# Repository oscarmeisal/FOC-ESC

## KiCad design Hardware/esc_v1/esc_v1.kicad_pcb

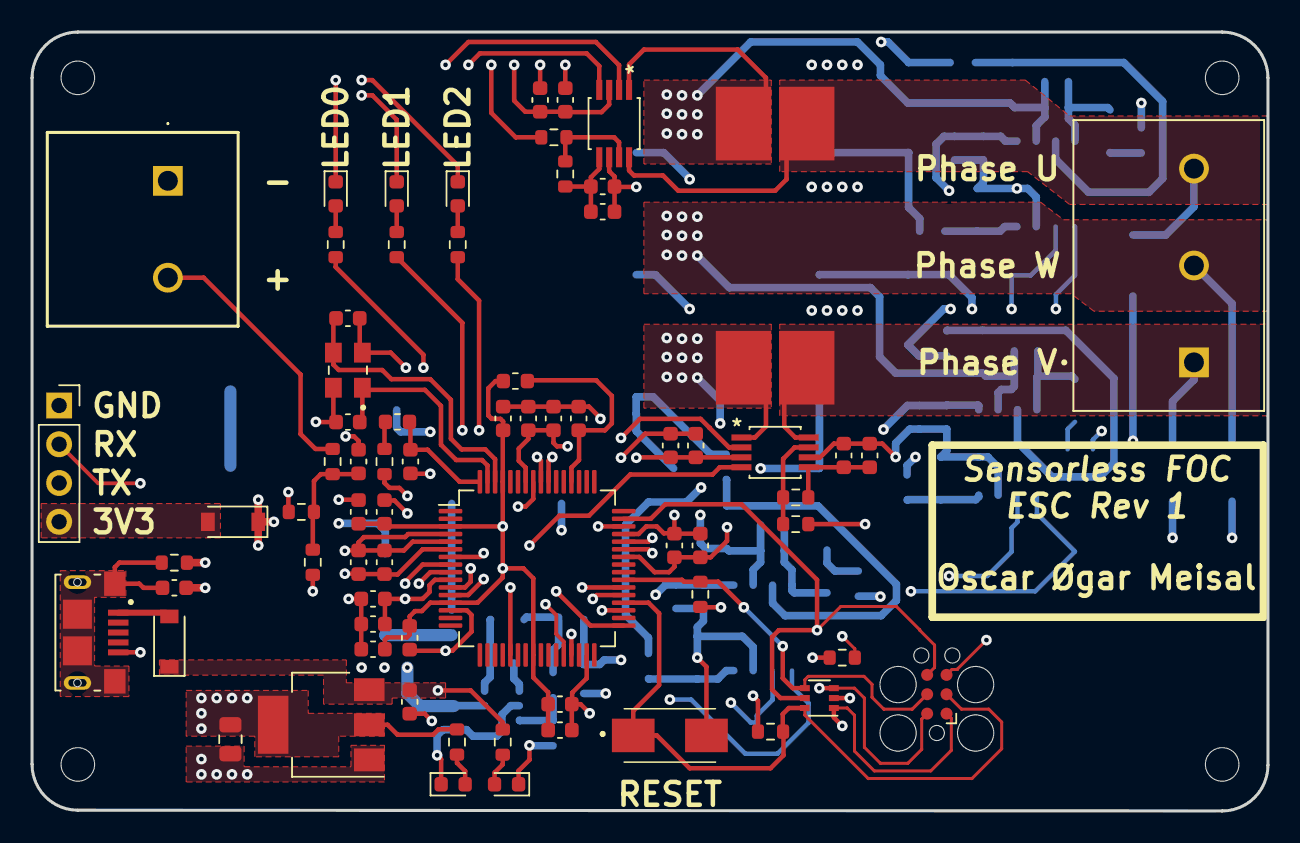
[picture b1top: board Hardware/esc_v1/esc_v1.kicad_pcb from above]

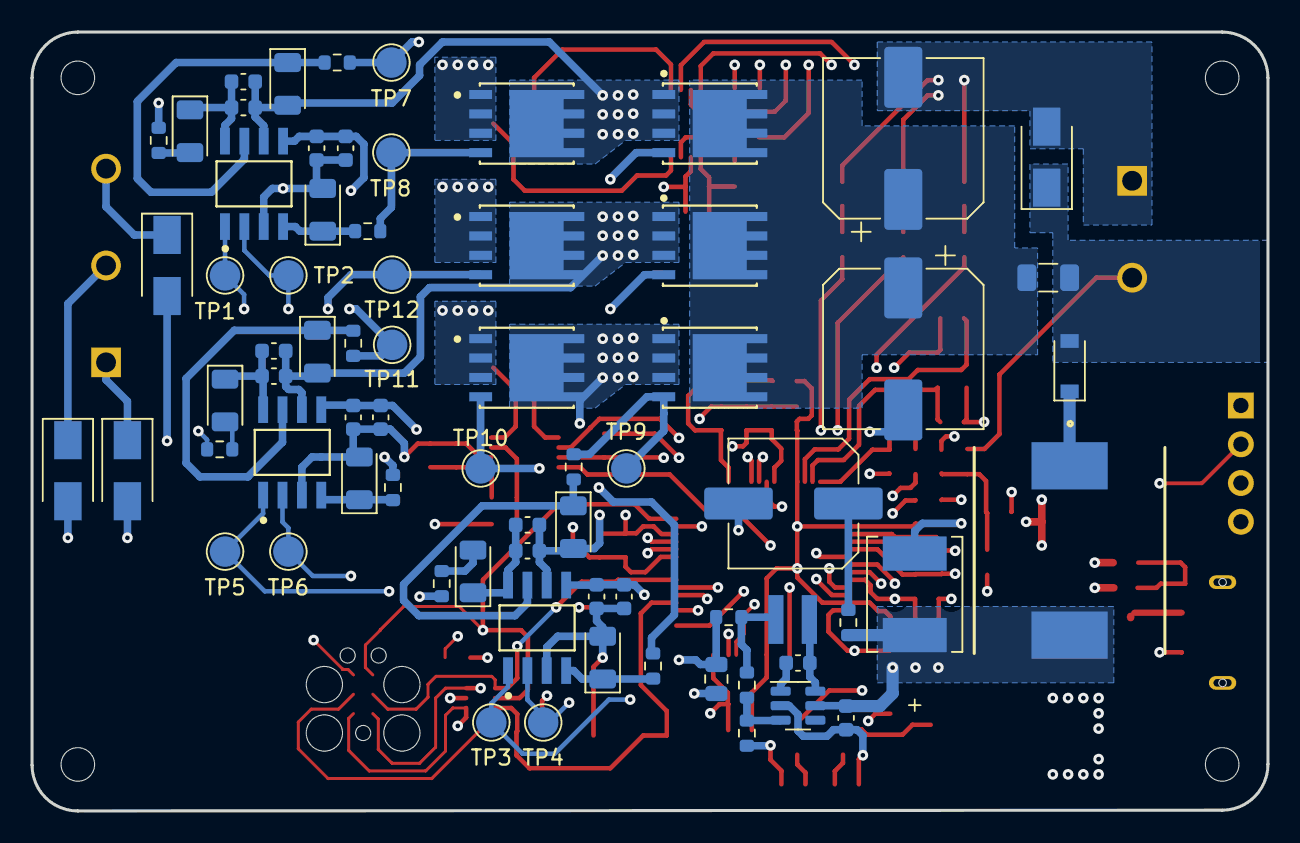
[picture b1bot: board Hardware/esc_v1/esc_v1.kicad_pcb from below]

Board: 6 copper layers, 81.0 x 51.1 mm, 146 parts (71 on the bottom side), 74 nets.

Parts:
C1, C11, C19: 4.7uF; C_0603_1608Metric
C2, C3: 10uF; C_0603_1608Metric
C4, C46, C48, C50, C52: 10nF; C_0603_1608Metric
C5: 100uF; T510E107M025AT E050
C6, C7: 22uF; C_0805_2012Metric
C8: 390uF, 20mOhm; C_Elec_8x10.2
C9, C12, C13, C14, C16, C17, C18, C20, C21, C22, C23, C24, C25, C26, C27, C28, C34, C38, C44: 100nF; C_0603_1608Metric
C10, C15, C29, C35, C36, C39, C42, C45, C47, C49, C51, C53: 1uF; C_0603_1608Metric
C33, C37, C43: 1000pF; C_0603_1608Metric
C40, C41: 270uF; CP_Elec_10x10
D1, D4, D10, D22: LED green; LED_0603_1608Metric
D2: PESD3V3L5UY; SOT-363_SC-70-6
D3, D6, D7, D8: TVS, 50V; D_SMA
D5: LED red; LED_0603_1608Metric
D9, D23, D24: D_Schottky; D_SOD-123
D13, D14, D15, D16, D17, D18, D19, D20, D21: D_Schottky; D_1206_3216Metric
F1: 40A; Fuse_1206_3216Metric
FB1: 470R@100MHz; L_0603_1608Metric
H1, H2, H3, H4: MountingHole; MountingHole_2.2mm_M2
J1: vcc_connector; 1714955
J2: SWD_tag_connect; Tag-Connect_TC2030-IDC-FP_2x03_P1.27mm_Vertical
J3: motor_connector; TE_796740-3
J4: 10118193-0001LF; FCI_10118193-0001LF
J5: Conn_01x04; PinSocket_1x04_P2.54mm_Vertical
L1: 10uH; Wuerth_Elektronik-744025100-Manufacturer_Recommended
L2: 10uH - 60mA; L_0603_1608Metric
L3: 47uH; SRP1265A
Q1, Q2, Q3, Q4, Q5, Q6: IRFH7084TRPBF; Infineon-PQFN5x6-G-02_2017-22-MFG
R1, R2, R3, R8, R10, R12: 1K; R_0603_1608Metric
R4: 1M; R_0603_1608Metric
R5: 62K; R_0603_1608Metric
R6: 11.8K; R_0603_1608Metric
R7: 4.7K; R_0603_1608Metric
R9, R11, R23, R26, R35: 0R; R_0603_1608Metric
R13: 2.2R; R_0603_1608Metric
R14, R15, R16: 33K; R_0603_1608Metric
R22: 1R; R_0603_1608Metric
R24, R25, R27, R34, R36, R37: 10R; R_0603_1608Metric
R28, R31: 2mOhm; WSHM28185L000FEA
R29, R32: 10K; R_0603_1608Metric
R30, R33: 15K; R_0603_1608Metric
SW1: SW_Push; 1478731
TP1, TP2, TP3, TP4, TP5, TP6, TP7, TP8, TP9, TP10, TP11, TP12: TestPoint; TestPoint_Pad_D2.0mm
U1, U3, U6: FAN7390MX; Fairchild-CASE_751EG-0-0-0
U2: AZ1117CH-3.3TRG1; SOT-223-3_TabPin2
U4: ATSAME70J21A-AN; LQFP-64_10x10mm_P0.5mm
U7: RT8259GE; SOT-23-6
U9, U10: MAX40056UAUA/V+; MAX40056UAUA&slash_V&plus_
Y1: Crystal_GND2; XTAL_ECS-120-10-33B-CKM-TR

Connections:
+3V3: C7.1, C11.1, C12.1, C14.1, C17.1, C20.1, C21.1, C25.1, C29.1, C46.1, C47.1, C50.1, C51.1, D2.1 (K1), D9.1 (K), J2.1, R10.1, R13.2, R14.2, R15.1, R16.1, U2.2 (VO), U4.4 (VDDIN), U4.5 (VREFP), U4.10 (VDDIO), U4.42 (VDDIO), U4.58 (VDDIO), U9.3 (VDD), U10.3 (VDD)
+5V: C3.1, C6.1, D23.1 (K), R11.2, R12.1, U2.3 (VI)
+BATT: D3.1, D24.2 (A), F1.1, J1.2, R7.1
/+BATT_filtered: C2.1, C5.1, C10.1, C33.1, C36.1, C37.1, C42.1, C43.1, L3.2, R22.1, R23.2, R26.2, R35.2, U1.5 (VDD), U3.5 (VDD), U6.5 (VDD), U7.5 (VIN)
/MCU/LED_0: R1.1, U4.57 (PD1)
/MCU/LED_1: R2.1, U4.56 (PD2)
/MCU/LED_2: R3.1, U4.55 (PD3)
/MCU/PWM_H0: TP1.1, U4.43 (PD11), U6.1 (HIN)
/MCU/PWM_H1: TP3.1, U1.1 (HIN), U4.29 (PA12)
/MCU/PWM_H2: TP5.1, U3.1 (HIN), U4.46 (PB4)
/MCU/PWM_L0: TP2.1, U4.44 (PD10), U6.2 (LIN)
/MCU/PWM_L1: TP4.1, U1.2 (LIN), U4.38 (PB12)
/MCU/PWM_L2: TP6.1, U3.2 (LIN), U4.21 (PD26)
/MCU/VDDCORE: C13.1, C15.1, C16.1, C18.1, C22.1, C23.1, C26.1, FB1.1, U4.3 (VDDOUT), U4.13 (VDDCORE), U4.24 (VDDCORE), U4.61 (VDDCORE)
/MCU/VDDPLL: C24.1, FB1.2, U4.52 (VDDPLL)
/MCU/VDDPLLUSB: C19.1, L2.2, U4.64 (VDDPLLUSB)
/MCU/V_sense: R9.2, U4.12 (PA21)
/MCU/XIN: C27.1, U4.63 (PB9), Y1.1
/MCU/XOUT: C28.1, U4.62 (PB8), Y1.3
/MCU/curr_sense_U: U4.9 (PB2), U9.4 (OUT)
/MCU/curr_sense_V: U4.11 (PB3), U10.4 (OUT)
/MCU/overcurr_err_U: U4.8 (PB0), U9.2 (COP)
/MCU/overcurr_err_V: U4.7 (PB1), U10.2 (COP)
/NRST: D2.6 (K5), J2.3, R16.2, SW1.1, U4.36 (NRST)
/PHASE_U: D8.1, J3.3, R28.2, U9.8 (RS-)
/PHASE_V: D6.1, J3.1, R31.2, U10.8 (RS-)
/PHASE_W: C38.2, C39.2, D7.1, D17.2 (A), J3.2, Q5.1 (S), Q5.2 (S), Q5.3 (S), Q6.5-6-7-8 (D), U3.6 (VS)
/Power/Feedback: R5.2, R6.1, U7.3 (FB)
/Powerstage/Gate_driver_U/Bootstrap+: C44.1, C45.1, D19.1 (K), U6.8 (VB)
/Powerstage/Gate_driver_U/GD_HO: D20.1 (K), R36.2, U6.7 (HO)
/Powerstage/Gate_driver_U/GD_LO: D21.1 (K), R37.2, U6.4 (LO)
/Powerstage/Gate_driver_U/HO: Q1.4 (G), R36.1, TP7.1
/Powerstage/Gate_driver_U/HS: C44.2, C45.2, D20.2 (A), Q1.1 (S), Q1.2 (S), Q1.3 (S), Q2.5-6-7-8 (D), R28.1, U6.6 (VS), U9.1 (RS+)
/Powerstage/Gate_driver_U/LO: Q2.4 (G), R37.1, TP8.1
/Powerstage/Gate_driver_V/Bootstrap+: C34.1, C35.1, D13.1 (K), U1.8 (VB)
/Powerstage/Gate_driver_V/GD_HO: D14.1 (K), R24.2, U1.7 (HO)
/Powerstage/Gate_driver_V/GD_LO: D15.1 (K), R25.2, U1.4 (LO)
/Powerstage/Gate_driver_V/HO: Q3.4 (G), R24.1, TP9.1
/Powerstage/Gate_driver_V/HS: C34.2, C35.2, D14.2 (A), Q3.1 (S), Q3.2 (S), Q3.3 (S), Q4.5-6-7-8 (D), R31.1, U1.6 (VS), U10.1 (RS+)
/Powerstage/Gate_driver_V/LO: Q4.4 (G), R25.1, TP10.1
/Powerstage/Gate_driver_W/Bootstrap+: C38.1, C39.1, D16.1 (K), U3.8 (VB)
/Powerstage/Gate_driver_W/GD_HO: D17.1 (K), R27.2, U3.7 (HO)
/Powerstage/Gate_driver_W/GD_LO: D18.1 (K), R34.2, U3.4 (LO)
/Powerstage/Gate_driver_W/HO: Q5.4 (G), R27.1, TP11.1
/Powerstage/Gate_driver_W/LO: Q6.4 (G), R34.1, TP12.1
/Powerstage/measurements_phase_U/Ref: C48.1, C49.1, R29.1, U9.5 (REF)
/Powerstage/measurements_phase_V/Ref: C52.1, C53.1, R32.1, U10.5 (REF)
/SWCLK: D2.4 (K3), J2.4, R15.2, U4.39 (PB7)
/SWDIO: D2.3 (K2), J2.2, R14.1, U4.35 (PB6)
/TRACESWO: D2.5 (K4), J2.6, U4.47 (PB5)
/UART0_RX: J5.2, U4.28 (PA10)
/UART0_TX: J5.3, U4.33 (PA9)
/VBUS: D23.2 (A), J4.1 (VUSB)
/shield: C1.1, J4.S1 (SHIELD), J4.S2 (SHIELD), J4.S3 (SHIELD), J4.S4 (SHIELD), J4.S5 (SHIELD), J4.S6 (SHIELD), R4.1
GND: C1.2, C2.2, C3.2, C5.2, C6.2, C7.2, C8.2, C9.2, C10.2, C11.2, C12.2, C13.2, C14.2, C15.2, C16.2, C17.2, C18.2, C19.2, C20.2, C21.2, C22.2, C23.2, C24.2, C25.2, C26.2, C27.2, C28.2, C29.2, C33.2, C36.2, C37.2, C40.2, C41.2, C42.2, C43.2, C46.2, C47.2, C48.2, C49.2, C50.2, C51.2, C52.2, C53.2, D1.1 (K), D2.2 (A), D3.2, D4.1 (K), D5.1 (K), D6.2, D7.2, D8.2, D10.1 (K), D15.2 (A), D18.2 (A), D21.2 (A), D22.1 (K), J1.1, J2.5, J4.5 (GND), J5.1, Q2.1 (S), Q2.2 (S), Q2.3 (S), Q4.1 (S), Q4.2 (S), Q4.3 (S), Q6.1 (S), Q6.2 (S), Q6.3 (S), R4.2, R6.2, R8.2, R30.2, R33.2, SW1.2, U1.3 (COM), U2.1 (GND), U3.3 (COM), U4.6 (GND), U4.14 (GND), U4.31 (GND), U4.37 (TST), U4.45 (JTAGSEL), U6.3 (COM), U7.2 (GND), U9.6 (GND), U10.6 (GND), Y1.2, Y1.4
unnamed: C4.1, U7.1 (BOOT)
unnamed: C4.2, L1.1, U7.6 (PHASE)
unnamed: C8.1, R22.2
unnamed: C9.1, R7.2, R8.1, R9.1
unnamed: C40.1, C41.1, F1.2, Q1.5-6-7-8 (D), Q3.5-6-7-8 (D), Q5.5-6-7-8 (D)
unnamed: D1.2 (A), R1.2
unnamed: D4.2 (A), R2.2
unnamed: D5.2 (A), R3.2
unnamed: D9.2 (A), J5.4
unnamed: D10.2 (A), R10.2
unnamed: D13.2 (A), R23.1
unnamed: D16.2 (A), R26.1
unnamed: D19.2 (A), R35.1
unnamed: D22.2 (A), R12.2
unnamed: D24.1 (K), L3.1
unnamed: L1.2, R5.1, R11.1
unnamed: L2.1, R13.1
unnamed: R29.2, R30.1, U9.7 (CIP)
unnamed: R32.2, R33.1, U10.7 (CIP)

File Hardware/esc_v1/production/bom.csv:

Designator,Footprint,Quantity,Value,LCSC Part #
J1,1714955,1,vcc_connector,
C51,C_0603_1608Metric,1,1uF,
C25,C_0603_1608Metric,1,100nF,
R1,R_0603_1608Metric,1,1K,
FB1,L_0603_1608Metric,1,470R@100MHz,
C7,C_0805_2012Metric,1,22uF,
R33,R_0603_1608Metric,1,15K,
C27,C_0603_1608Metric,1,100nF,
C28,C_0603_1608Metric,1,100nF,
Y1,XTAL_ECS-120-10-33B-CKM-TR,1,Crystal_GND2,
H1,MountingHole_2.2mm_M2,1,MountingHole,
C49,C_0603_1608Metric,1,1uF,
U10,MAX40056UAUA&slash_V&plus_,1,MAX40056UAUA/V+,
D10,LED_0603_1608Metric,1,LED green,
R2,R_0603_1608Metric,1,1K,
C52,C_0603_1608Metric,1,10nF,
C53,C_0603_1608Metric,1,1uF,
D1,LED_0603_1608Metric,1,LED green,
C47,C_0603_1608Metric,1,1uF,
U2,SOT-223-3_TabPin2,1,AZ1117CH-3.3TRG1,
D4,LED_0603_1608Metric,1,LED green,
D5,LED_0603_1608Metric,1,LED red,
C22,C_0603_1608Metric,1,100nF,
R10,R_0603_1608Metric,1,1K,
R12,R_0603_1608Metric,1,1K,
L2,L_0603_1608Metric,1,10uH - 60mA,
C24,C_0603_1608Metric,1,100nF,
C17,C_0603_1608Metric,1,100nF,
C20,C_0603_1608Metric,1,100nF,
C15,C_0603_1608Metric,1,1uF,
J3,TE_796740-3,1,motor_connector,
C19,C_0603_1608Metric,1,4.7uF,
R3,R_0603_1608Metric,1,1K,
R9,R_0603_1608Metric,1,0R,
C13,C_0603_1608Metric,1,100nF,
C12,C_0603_1608Metric,1,100nF,
J4,FCI_10118193-0001LF,1,10118193-0001LF,
R15,R_0603_1608Metric,1,33K,
SW1,1478731,1,SW_Push,
R29,R_0603_1608Metric,1,10K,
D9,D_SOD-123,1,D_Schottky,
C9,C_0603_1608Metric,1,100nF,
C46,C_0603_1608Metric,1,10nF,
J2,Tag-Connect_TC2030-IDC-FP_2x03_P1.27mm_Vertical,1,SWD_tag_connect,
D2,SOT-363_SC-70-6,1,PESD3V3L5UY,
C3,C_0603_1608Metric,1,10uF,
C14,C_0603_1608Metric,1,100nF,
C23,C_0603_1608Metric,1,100nF,
D23,D_SOD-123,1,D_Schottky,
R14,R_0603_1608Metric,1,33K,
C50,C_0603_1608Metric,1,10nF,
H2,MountingHole_2.2mm_M2,1,MountingHole,
H4,MountingHole_2.2mm_M2,1,MountingHole,
U4,LQFP-64_10x10mm_P0.5mm,1,ATSAME70J21A-AN,
C26,C_0603_1608Metric,1,100nF,
J5,PinSocket_1x04_P2.54mm_Vertical,1,Conn_01x04,
C21,C_0603_1608Metric,1,100nF,
R31,WSHM28185L000FEA,1,2mOhm,
H3,MountingHole_2.2mm_M2,1,MountingHole,
R32,R_0603_1608Metric,1,10K,
C11,C_0603_1608Metric,1,4.7uF,
R13,R_0603_1608Metric,1,2.2R,
R30,R_0603_1608Metric,1,15K,
R28,WSHM28185L000FEA,1,2mOhm,
R8,R_0603_1608Metric,1,1K,
C16,C_0603_1608Metric,1,100nF,
R16,R_0603_1608Metric,1,33K,
R4,R_0603_1608Metric,1,1M,
R7,R_0603_1608Metric,1,4.7K,
C48,C_0603_1608Metric,1,10nF,
D22,LED_0603_1608Metric,1,LED green,
C29,C_0603_1608Metric,1,1uF,
C18,C_0603_1608Metric,1,100nF,
C1,C_0603_1608Metric,1,4.7uF,
U9,MAX40056UAUA&slash_V&plus_,1,MAX40056UAUA/V+,
TP4,TestPoint_Pad_D2.0mm,1,TestPoint,
C5,T510E107M025AT E050,1,100uF,
TP6,TestPoint_Pad_D2.0mm,1,TestPoint,
Q2,Infineon-PQFN5x6-G-02_2017-22-MFG,1,IRFH7084TRPBF,
C44,C_0603_1608Metric,1,100nF,
Q1,Infineon-PQFN5x6-G-02_2017-22-MFG,1,IRFH7084TRPBF,
R22,R_0603_1608Metric,1,1R,
C43,C_0603_1608Metric,1,1000pF,
D3,D_SMA,1,"TVS, 50V",
R25,R_0603_1608Metric,1,10R,
C38,C_0603_1608Metric,1,100nF,
U3,Fairchild-CASE_751EG-0-0-0,1,FAN7390MX,
R6,R_0603_1608Metric,1,11.8K,
C45,C_0603_1608Metric,1,1uF,
C8,C_Elec_8x10.2,1,"390uF, 20mOhm",
Q3,Infineon-PQFN5x6-G-02_2017-22-MFG,1,IRFH7084TRPBF,
Q5,Infineon-PQFN5x6-G-02_2017-22-MFG,1,IRFH7084TRPBF,
R36,R_0603_1608Metric,1,10R,
R11,R_0603_1608Metric,1,0R,
F1,Fuse_1206_3216Metric,1,40A,
TP9,TestPoint_Pad_D2.0mm,1,TestPoint,
R23,R_0603_1608Metric,1,0R,
Q6,Infineon-PQFN5x6-G-02_2017-22-MFG,1,IRFH7084TRPBF,
TP3,TestPoint_Pad_D2.0mm,1,TestPoint,
D24,D_SOD-123,1,D_Schottky,
C36,C_0603_1608Metric,1,1uF,
C42,C_0603_1608Metric,1,1uF,
L1,Wuerth_Elektronik-744025100-Manufacturer_Recommended,1,10uH,
TP12,TestPoint_Pad_D2.0mm,1,TestPoint,
L3,SRP1265A,1,47uH,
TP2,TestPoint_Pad_D2.0mm,1,TestPoint,
D15,D_1206_3216Metric,1,D_Schottky,
C4,C_0603_1608Metric,1,10nF,
D21,D_1206_3216Metric,1,D_Schottky,
R27,R_0603_1608Metric,1,10R,
C6,C_0805_2012Metric,1,22uF,
D8,D_SMA,1,"TVS, 50V",
R24,R_0603_1608Metric,1,10R,
D20,D_1206_3216Metric,1,D_Schottky,
TP10,TestPoint_Pad_D2.0mm,1,TestPoint,
D13,D_1206_3216Metric,1,D_Schottky,
D7,D_SMA,1,"TVS, 50V",
C37,C_0603_1608Metric,1,1000pF,
TP11,TestPoint_Pad_D2.0mm,1,TestPoint,
R26,R_0603_1608Metric,1,0R,
C2,C_0603_1608Metric,1,10uF,
R34,R_0603_1608Metric,1,10R,
R35,R_0603_1608Metric,1,0R,
D19,D_1206_3216Metric,1,D_Schottky,
R5,R_0603_1608Metric,1,62K,
C39,C_0603_1608Metric,1,1uF,
C34,C_0603_1608Metric,1,100nF,
U7,SOT-23-6,1,RT8259GE,
TP5,TestPoint_Pad_D2.0mm,1,TestPoint,
C10,C_0603_1608Metric,1,1uF,
TP8,TestPoint_Pad_D2.0mm,1,TestPoint,
C41,CP_Elec_10x10,1,270uF,
C40,CP_Elec_10x10,1,270uF,
D18,D_1206_3216Metric,1,D_Schottky,
TP7,TestPoint_Pad_D2.0mm,1,TestPoint,
U6,Fairchild-CASE_751EG-0-0-0,1,FAN7390MX,
D6,D_SMA,1,"TVS, 50V",
U1,Fairchild-CASE_751EG-0-0-0,1,FAN7390MX,
TP1,TestPoint_Pad_D2.0mm,1,TestPoint,
D16,D_1206_3216Metric,1,D_Schottky,
D14,D_1206_3216Metric,1,D_Schottky,
D17,D_1206_3216Metric,1,D_Schottky,
C35,C_0603_1608Metric,1,1uF,
Q4,Infineon-PQFN5x6-G-02_2017-22-MFG,1,IRFH7084TRPBF,
C33,C_0603_1608Metric,1,1000pF,
R37,R_0603_1608Metric,1,10R,

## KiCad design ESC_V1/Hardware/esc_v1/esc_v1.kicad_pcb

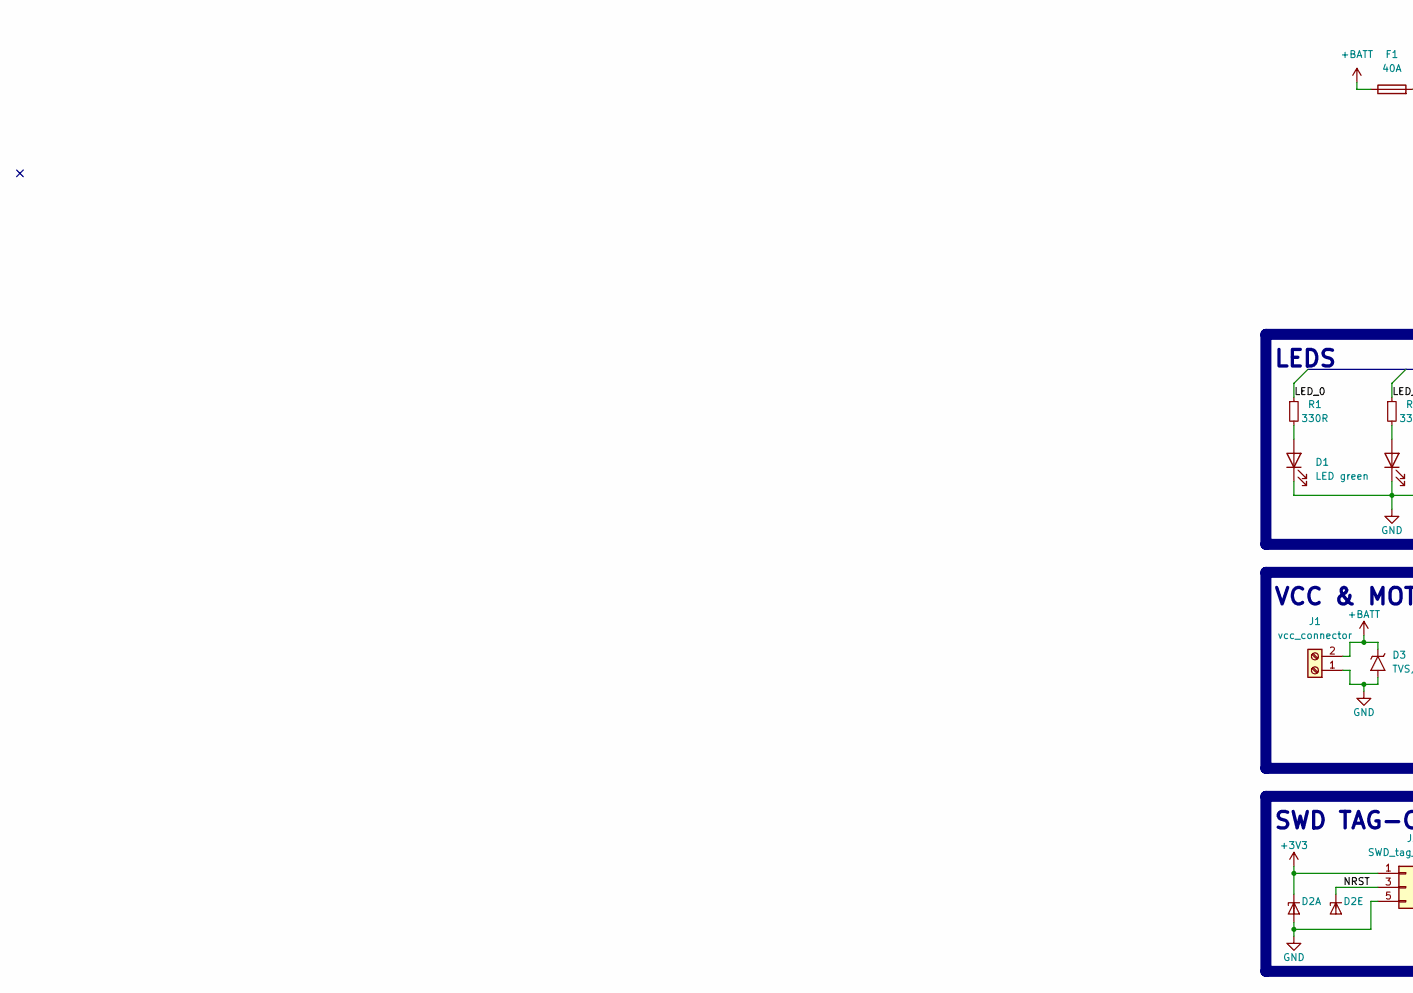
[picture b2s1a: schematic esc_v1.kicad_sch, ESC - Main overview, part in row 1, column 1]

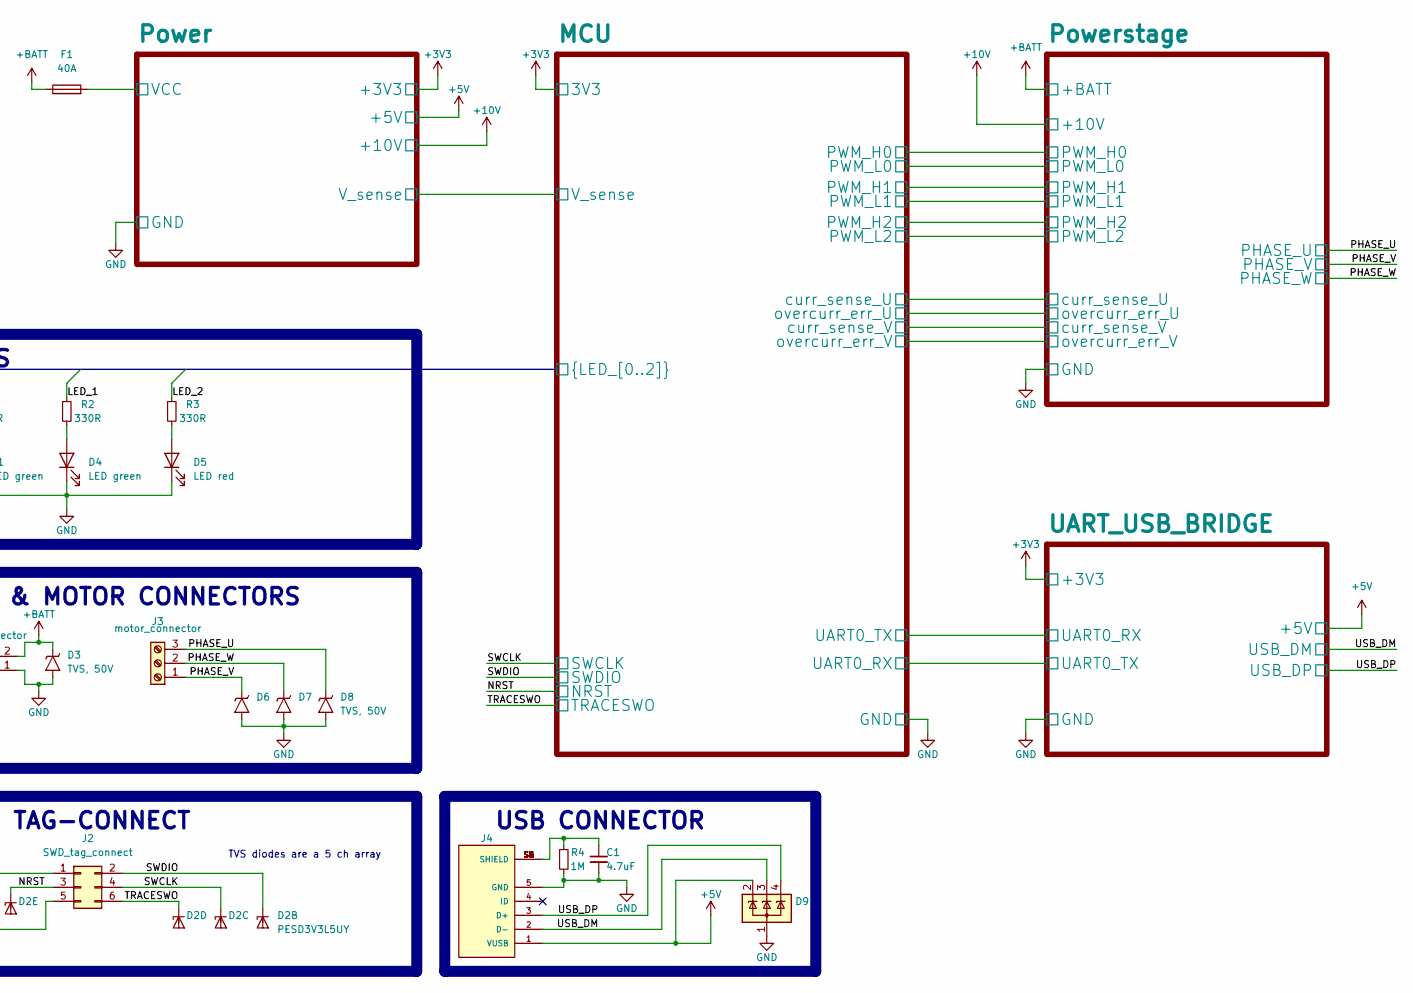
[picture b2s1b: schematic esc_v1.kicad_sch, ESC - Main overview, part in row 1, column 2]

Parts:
C1: 4.7uF; C_0603_1608Metric
D1, D4: LED green; LED_0603_1608Metric
D2: PESD3V3L5UY; SOT-363_SC-70-6
D3, D6, D7, D8: TVS, 50V; D_SMA
D5: LED red; LED_0603_1608Metric
D9: SP0503BAHT; SOT-143
F1: 40A; Fuse_1206_3216Metric; Part no 0685P9400-01
J1: vcc_connector; 1714955; Part no 1714955
J2: SWD_tag_connect; Tag-Connect_TC2030-IDC-FP_2x03_P1.27mm_Vertical
J3: motor_connector; TE_796740-3; Part no 796740-3
J4: 10118193-0001LF; FCI_10118193-0001LF
R1, R2, R3: 330R; R_0603_1608Metric
R4: 1M; R_0603_1608Metric

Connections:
+BATT: D3.1, F1.1, J1.2; also elsewhere on the board
/MCU/LED_0: R1.1; also elsewhere on the board
/MCU/LED_1: R2.1; also elsewhere on the board
/MCU/LED_2: R3.1; also elsewhere on the board
/NRST: D2.6 (K5), J2.3; also elsewhere on the board
/PHASE_U: D8.1, J3.3; also elsewhere on the board
/PHASE_V: D6.1, J3.1; also elsewhere on the board
/PHASE_W: D7.1, J3.2; also elsewhere on the board
/SWCLK: D2.4 (K3), J2.4; also elsewhere on the board
/SWDIO: D2.3 (K2), J2.2; also elsewhere on the board
/TRACESWO: D2.5 (K4), J2.6; also elsewhere on the board
/USB_DM: D9.3 (K), J4.2 (D-); also elsewhere on the board
/USB_DP: D9.4 (K), J4.3 (D+); also elsewhere on the board
GND: C1.2, D1.1 (K), D2.2 (A), D3.2, D4.1 (K), D5.1 (K), D6.2, D7.2, D8.2, D9.1 (A), J1.1, J2.5, J4.5 (GND), R4.2; also elsewhere on the board
unnamed: C1.1, J4.S1 (SHIELD), J4.S2 (SHIELD), J4.S3 (SHIELD), J4.S4 (SHIELD), J4.S5 (SHIELD), J4.S6 (SHIELD), R4.1
unnamed: D1.2 (A), R1.2
unnamed: D4.2 (A), R2.2
unnamed: D5.2 (A), R3.2
VCC: F1.2; also elsewhere on the board

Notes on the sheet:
USB CONNECTOR
VCC & MOTOR CONNECTORS
LEDS
SWD TAG-CONNECT
TVS diodes are a 5 ch array

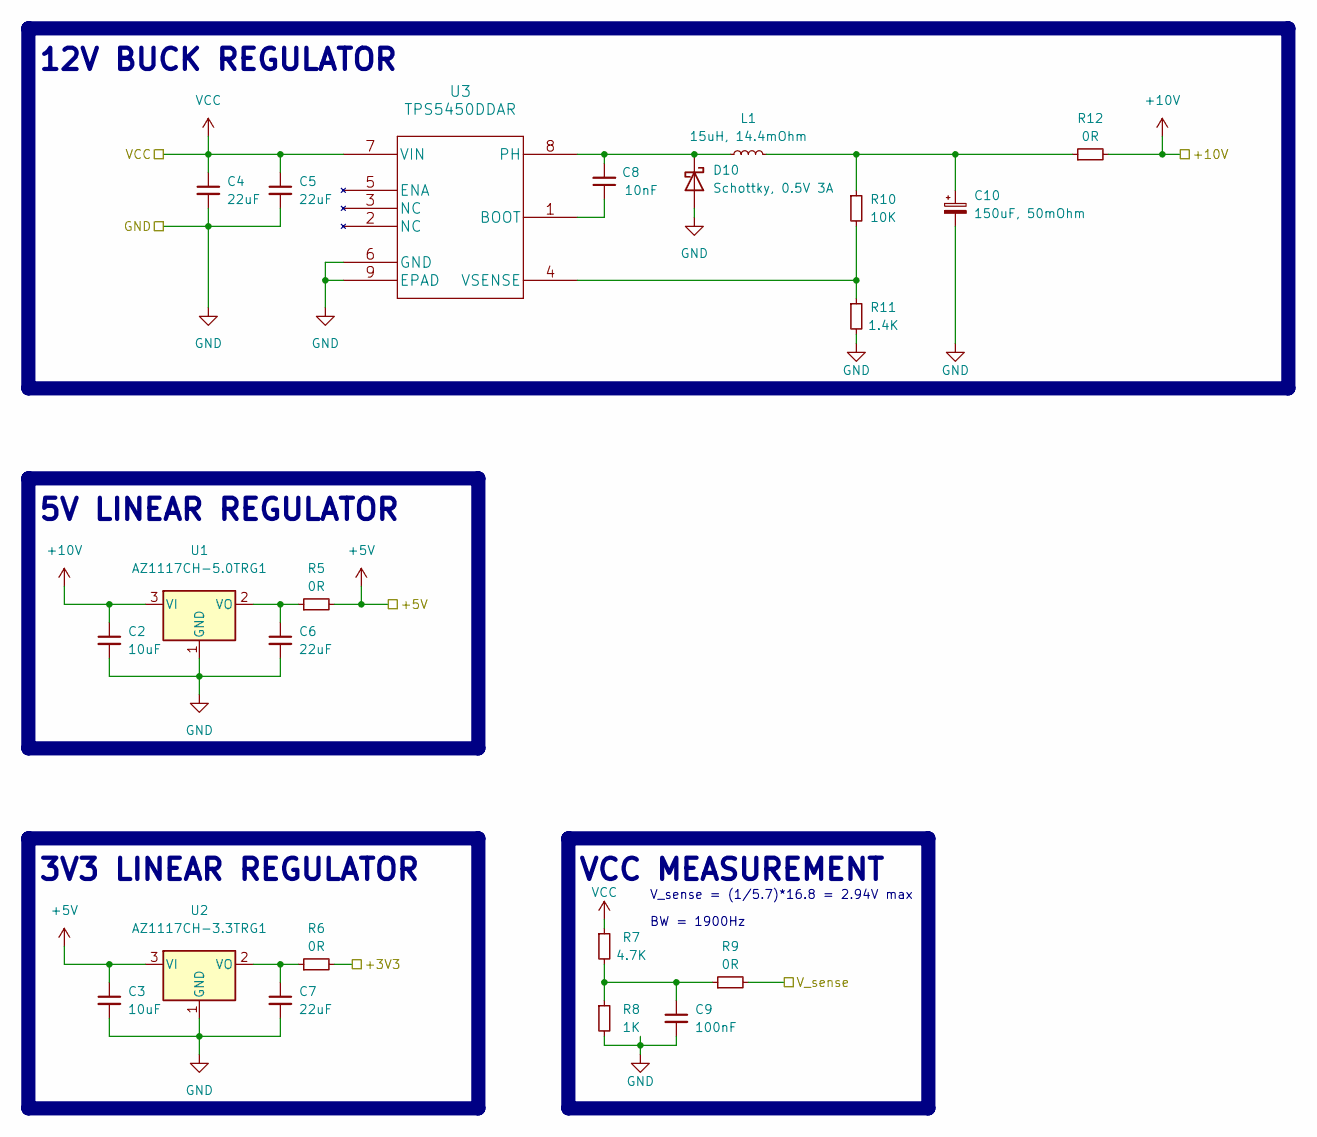
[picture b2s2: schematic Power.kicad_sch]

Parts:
C2, C3: 10uF; C_0603_1608Metric
C4, C5, C6, C7: 22uF; C_0603_1608Metric
C8: 10nF; C_0603_1608Metric
C9: 100nF; C_0603_1608Metric
C10: 150uF, 50mOhm; T510E107M025AT E050; PartNo T510E107M025ATE050
D10: Schottky, 0.5V 3A; D_SMA; Part no CDBA340-HF
L1: 15uH, 14.4mOhm; INDPM172172X700N; Part No IHLP6767GZER150M11
R5, R6, R9, R12: 0R; R_0603_1608Metric
R7: 4.7K; R_0603_1608Metric
R8: 1K; R_0603_1608Metric
R10: 10K; R_0603_1608Metric
R11: 1.4K; R_0603_1608Metric
U1: AZ1117CH-5.0TRG1; SOT-223-3_TabPin2
U2: AZ1117CH-3.3TRG1; SOT-223-3_TabPin2
U3: TPS5450DDAR; TI_SO-PowerPAD-8

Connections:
/MCU/V_sense: R9.2; also elsewhere on the board
GND: C2.2, C3.2, C4.2, C5.2, C6.2, C7.2, C9.2, C10.2, D10.2 (A), R8.2, R11.2, U1.1 (GND), U2.1 (GND), U3.6 (GND), U3.9 (EPAD); also elsewhere on the board
unnamed: C8.1, U3.1 (BOOT)
unnamed: C8.2, D10.1 (K), L1.1, U3.8 (PH)
unnamed: C9.1, R7.2, R8.1, R9.1
unnamed: R10.2, R11.1, U3.4 (VSENSE)
VCC: C4.1, C5.1, R7.1, U3.7 (VIN); also elsewhere on the board

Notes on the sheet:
3V3 LINEAR REGULATOR
VCC MEASUREMENT
BW = 1900Hz
5V LINEAR REGULATOR
V_sense = (1/5.7)*16.8 = 2.94V max
12V BUCK REGULATOR

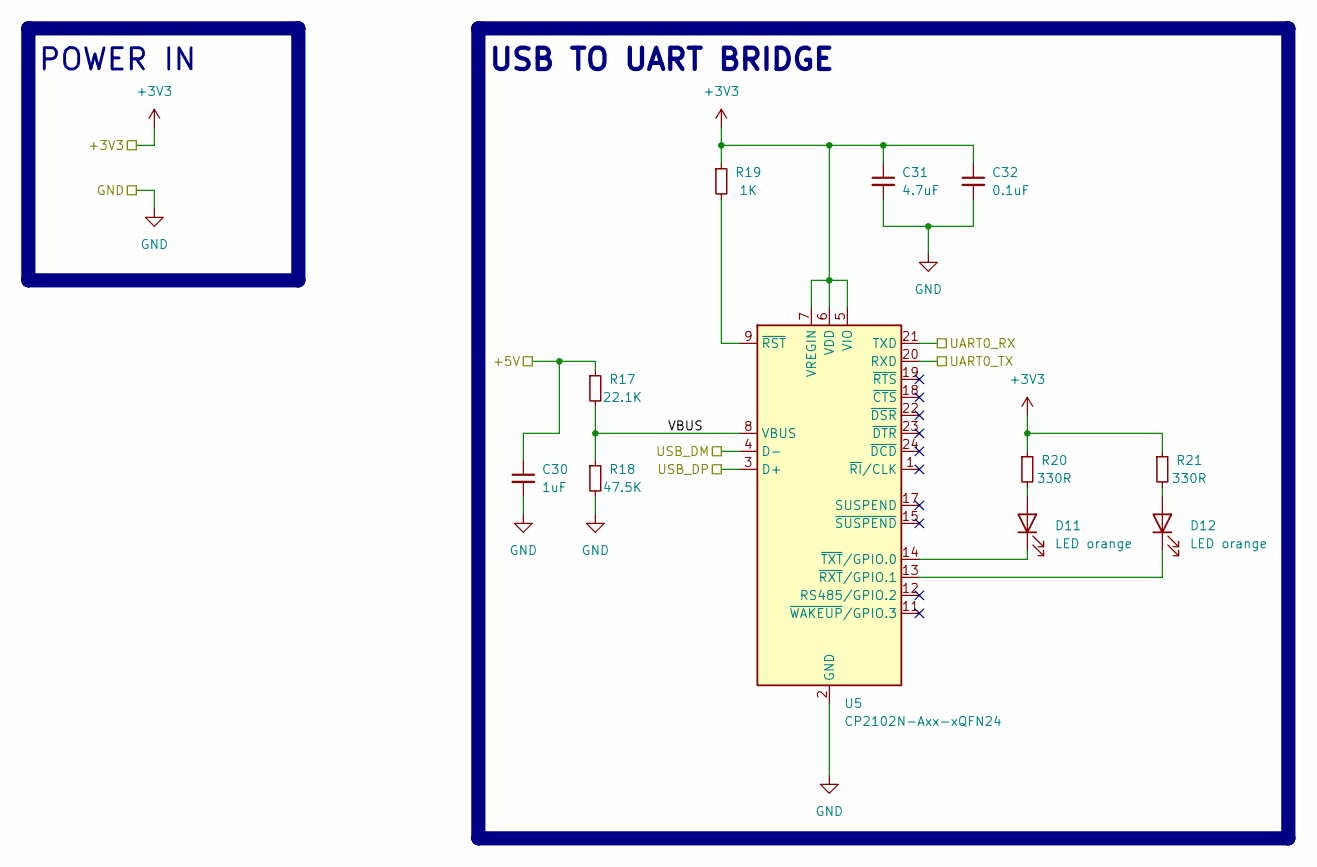
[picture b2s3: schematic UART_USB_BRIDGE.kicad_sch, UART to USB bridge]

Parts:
C30: 1uF; C_0603_1608Metric
C31: 4.7uF; C_0603_1608Metric
C32: 0.1uF; C_0603_1608Metric
D11, D12: LED orange; LED_0603_1608Metric
R17: 22.1K; R_0603_1608Metric
R18: 47.5K; R_0603_1608Metric
R19: 1K; R_0603_1608Metric
R20, R21: 330R; R_0603_1608Metric
U5: CP2102N-Axx-xQFN24; QFN-24-1EP_4x4mm_P0.5mm_EP2.6x2.6mm

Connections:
/MCU/UART0_RX: U5.20 (RXD); also elsewhere on the board
/MCU/UART0_TX: U5.21 (TXD); also elsewhere on the board
/UART_USB_BRIDGE/VBUS: R17.2, R18.1, U5.8 (VBUS)
/USB_DM: U5.4 (D-); also elsewhere on the board
/USB_DP: U5.3 (D+); also elsewhere on the board
GND: C30.2, C31.2, C32.2, R18.2, U5.2 (GND), U5.25 (GND); also elsewhere on the board
unnamed: D11.1 (K), U5.14 (~TXT/GPIO.0)
unnamed: D11.2 (A), R20.2
unnamed: D12.1 (K), U5.13 (~RXT/GPIO.1)
unnamed: D12.2 (A), R21.2
unnamed: R19.2, U5.9 (~RST)

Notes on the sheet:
POWER IN
USB TO UART BRIDGE

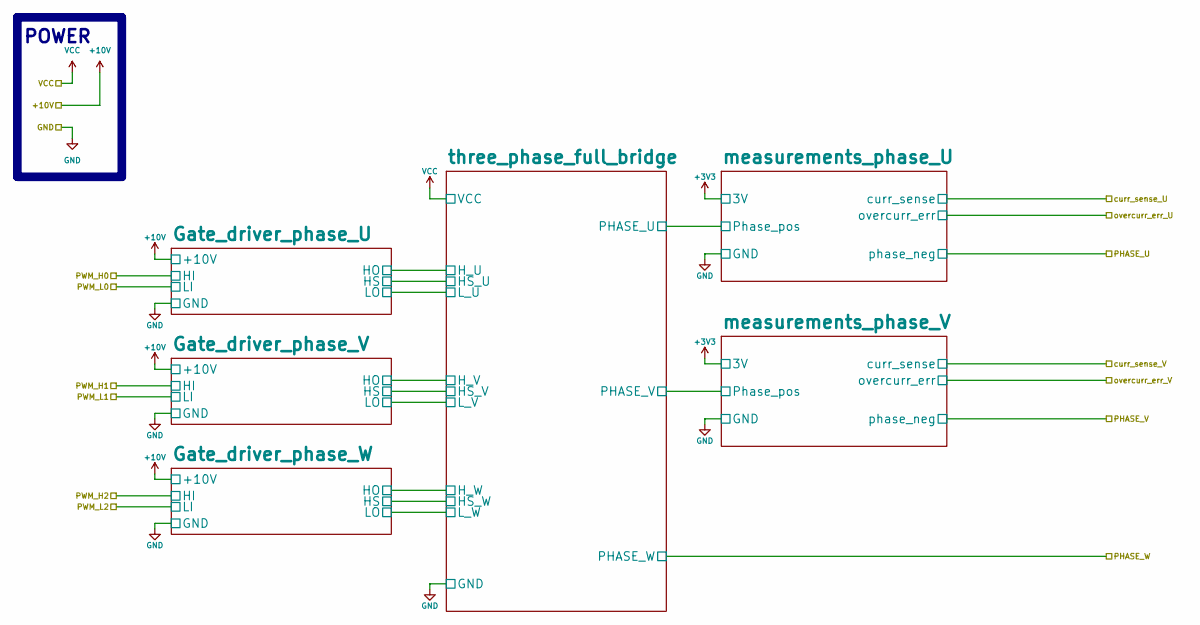
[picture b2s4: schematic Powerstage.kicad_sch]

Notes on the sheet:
POWER

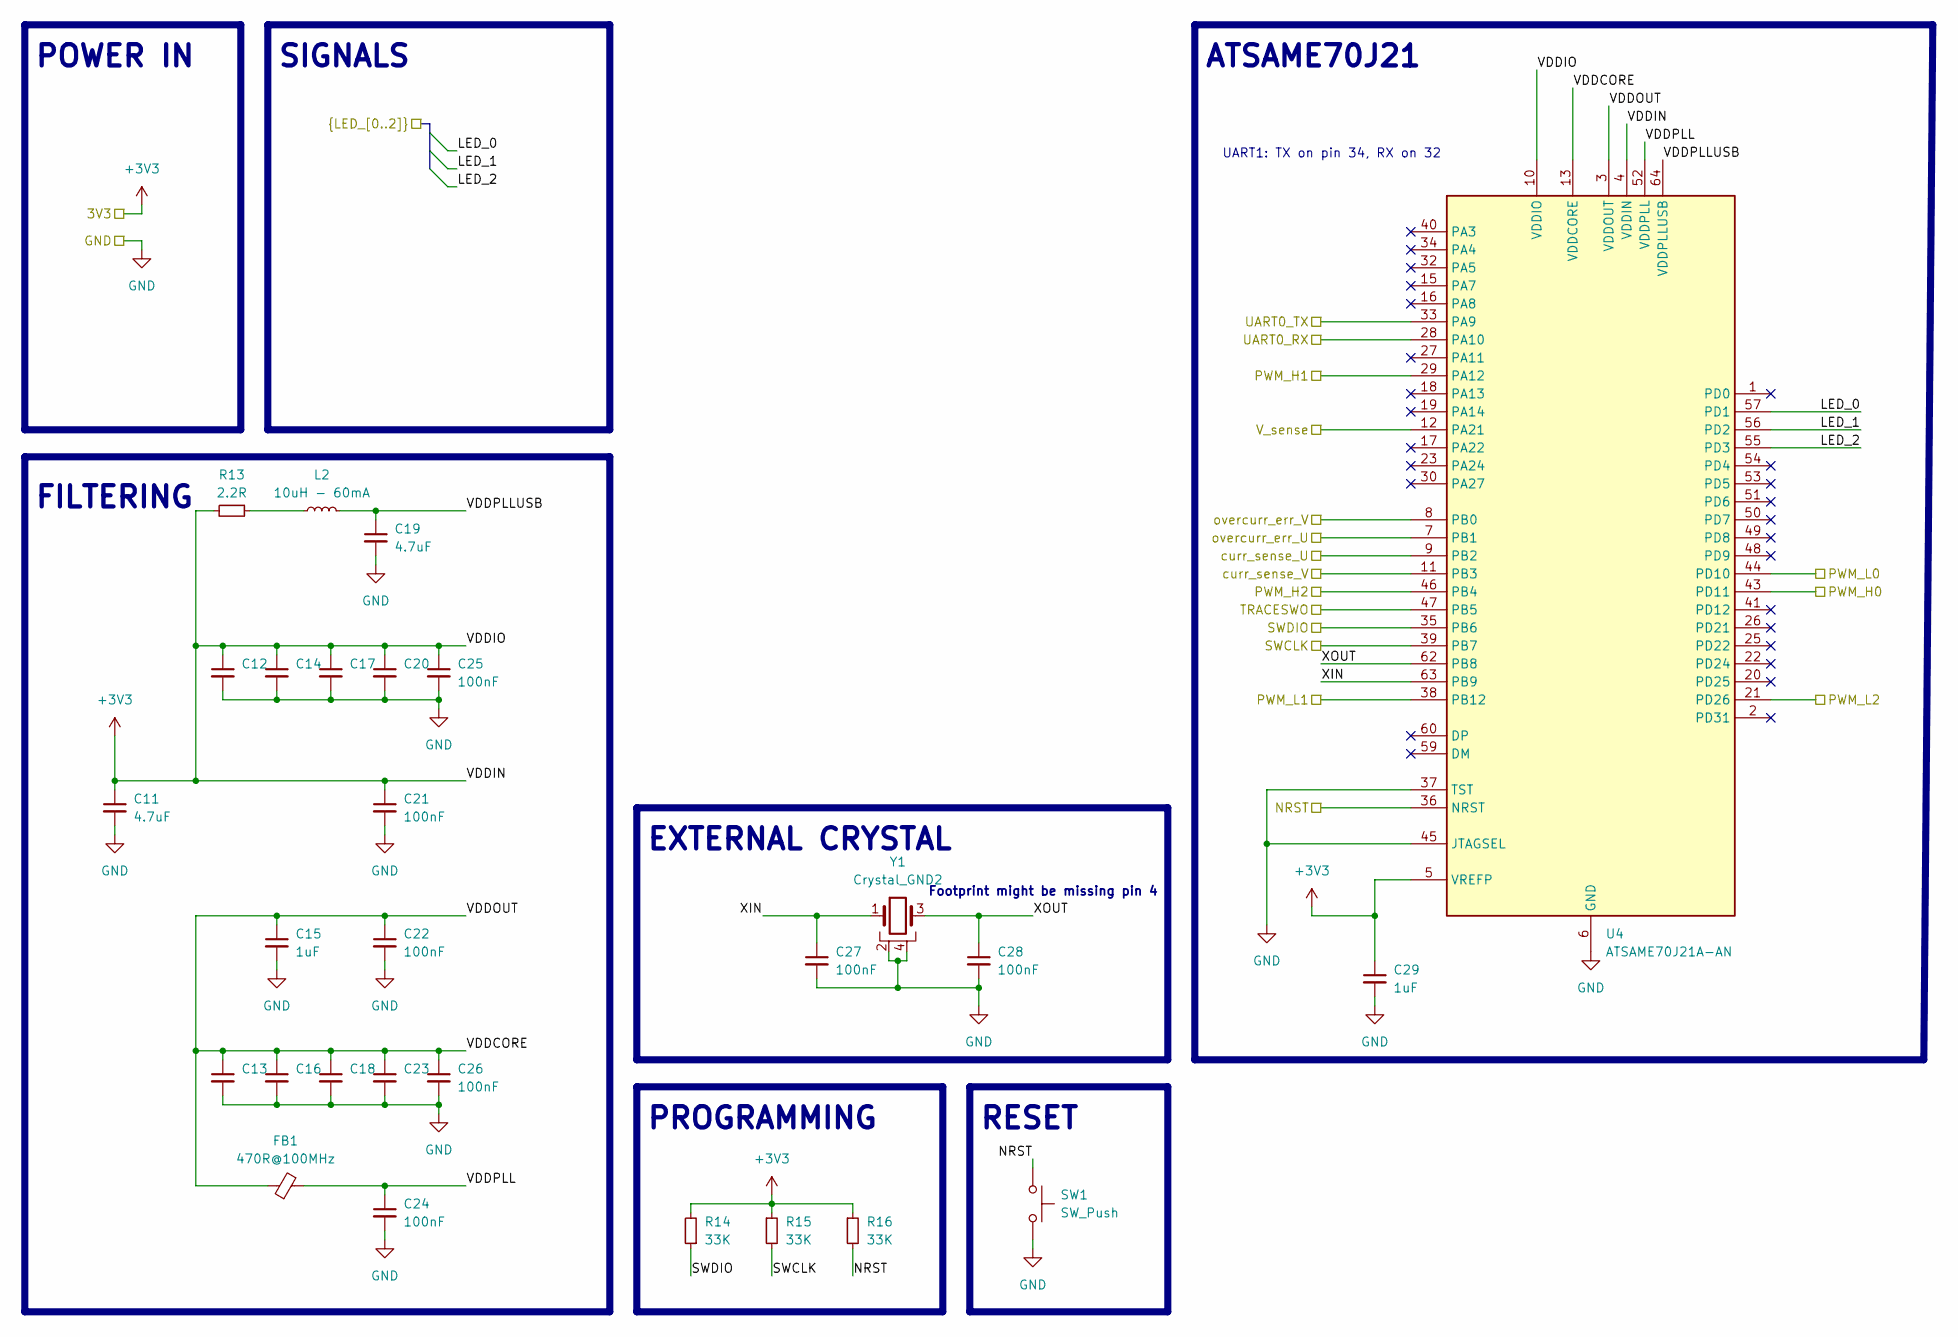
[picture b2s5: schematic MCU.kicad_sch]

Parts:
C11, C19: 4.7uF; C_0603_1608Metric
C12, C13, C14, C16, C17, C18, C20, C21, C22, C23, C24, C25, C26, C27, C28: 100nF; C_0603_1608Metric
C15, C29: 1uF; C_0603_1608Metric
FB1: 470R@100MHz; L_0603_1608Metric; Part no BLM18KG471SN1D
L2: 10uH - 60mA; L_0201_0603Metric; Part no LB1608T100M
R13: 2.2R; R_0603_1608Metric
R14, R15, R16: 33K; R_0603_1608Metric
SW1: SW_Push; 1478731; Part no FSM2JMTR
U4: ATSAME70J21A-AN; LQFP-64_10x10mm_P0.5mm
Y1: Crystal_GND2; XTAL_ECS-120-10-33B-CKM-TR; Part no ECS-120-10-33B-CKM-TR

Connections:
/MCU/LED_0: U4.57 (PD1); also elsewhere on the board
/MCU/LED_1: U4.56 (PD2); also elsewhere on the board
/MCU/LED_2: U4.55 (PD3); also elsewhere on the board
/MCU/PWM_H0: U4.43 (PD11); also elsewhere on the board
/MCU/PWM_H1: U4.29 (PA12); also elsewhere on the board
/MCU/PWM_H2: U4.46 (PB4); also elsewhere on the board
/MCU/PWM_L0: U4.44 (PD10); also elsewhere on the board
/MCU/PWM_L1: U4.38 (PB12); also elsewhere on the board
/MCU/PWM_L2: U4.21 (PD26); also elsewhere on the board
/MCU/UART0_RX: U4.28 (PA10); also elsewhere on the board
/MCU/UART0_TX: U4.33 (PA9); also elsewhere on the board
/MCU/VDDCORE: C13.1, C15.1, C16.1, C18.1, C22.1, C23.1, C26.1, FB1.1, U4.3 (VDDOUT), U4.13 (VDDCORE), U4.24 (VDDCORE), U4.61 (VDDCORE)
/MCU/VDDPLL: C24.1, FB1.2, U4.52 (VDDPLL)
/MCU/VDDPLLUSB: C19.1, L2.2, U4.64 (VDDPLLUSB)
/MCU/V_sense: U4.12 (PA21); also elsewhere on the board
/MCU/XIN: C27.1, U4.63 (PB9), Y1.1
/MCU/XOUT: C28.1, U4.62 (PB8), Y1.3
/MCU/curr_sense_U: U4.9 (PB2); also elsewhere on the board
/MCU/curr_sense_V: U4.11 (PB3); also elsewhere on the board
/MCU/overcurr_err_U: U4.7 (PB1); also elsewhere on the board
/MCU/overcurr_err_V: U4.8 (PB0); also elsewhere on the board
/NRST: R16.2, SW1.1, U4.36 (NRST); also elsewhere on the board
/SWCLK: R15.2, U4.39 (PB7); also elsewhere on the board
/SWDIO: R14.1, U4.35 (PB6); also elsewhere on the board
/TRACESWO: U4.47 (PB5); also elsewhere on the board
GND: C11.2, C12.2, C13.2, C14.2, C15.2, C16.2, C17.2, C18.2, C19.2, C20.2, C21.2, C22.2, C23.2, C24.2, C25.2, C26.2, C27.2, C28.2, C29.2, SW1.2, U4.6 (GND), U4.14 (GND), U4.31 (GND), U4.37 (TST), U4.45 (JTAGSEL), Y1.2, Y1.4; also elsewhere on the board
unnamed: L2.1, R13.1

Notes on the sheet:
POWER IN
ATSAME70J21
SIGNALS
EXTERNAL CRYSTAL
UART1: TX on pin 34, RX on 32
RESET
Footprint might be missing pin 4
PROGRAMMING
FILTERING

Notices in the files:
parts and their libraries:
Copyright 2021 Accelerated Designs. All rights reserved.
